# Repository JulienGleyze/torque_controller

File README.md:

## This repo contains the kicad project for my actuator's pcb controller, actuator image below

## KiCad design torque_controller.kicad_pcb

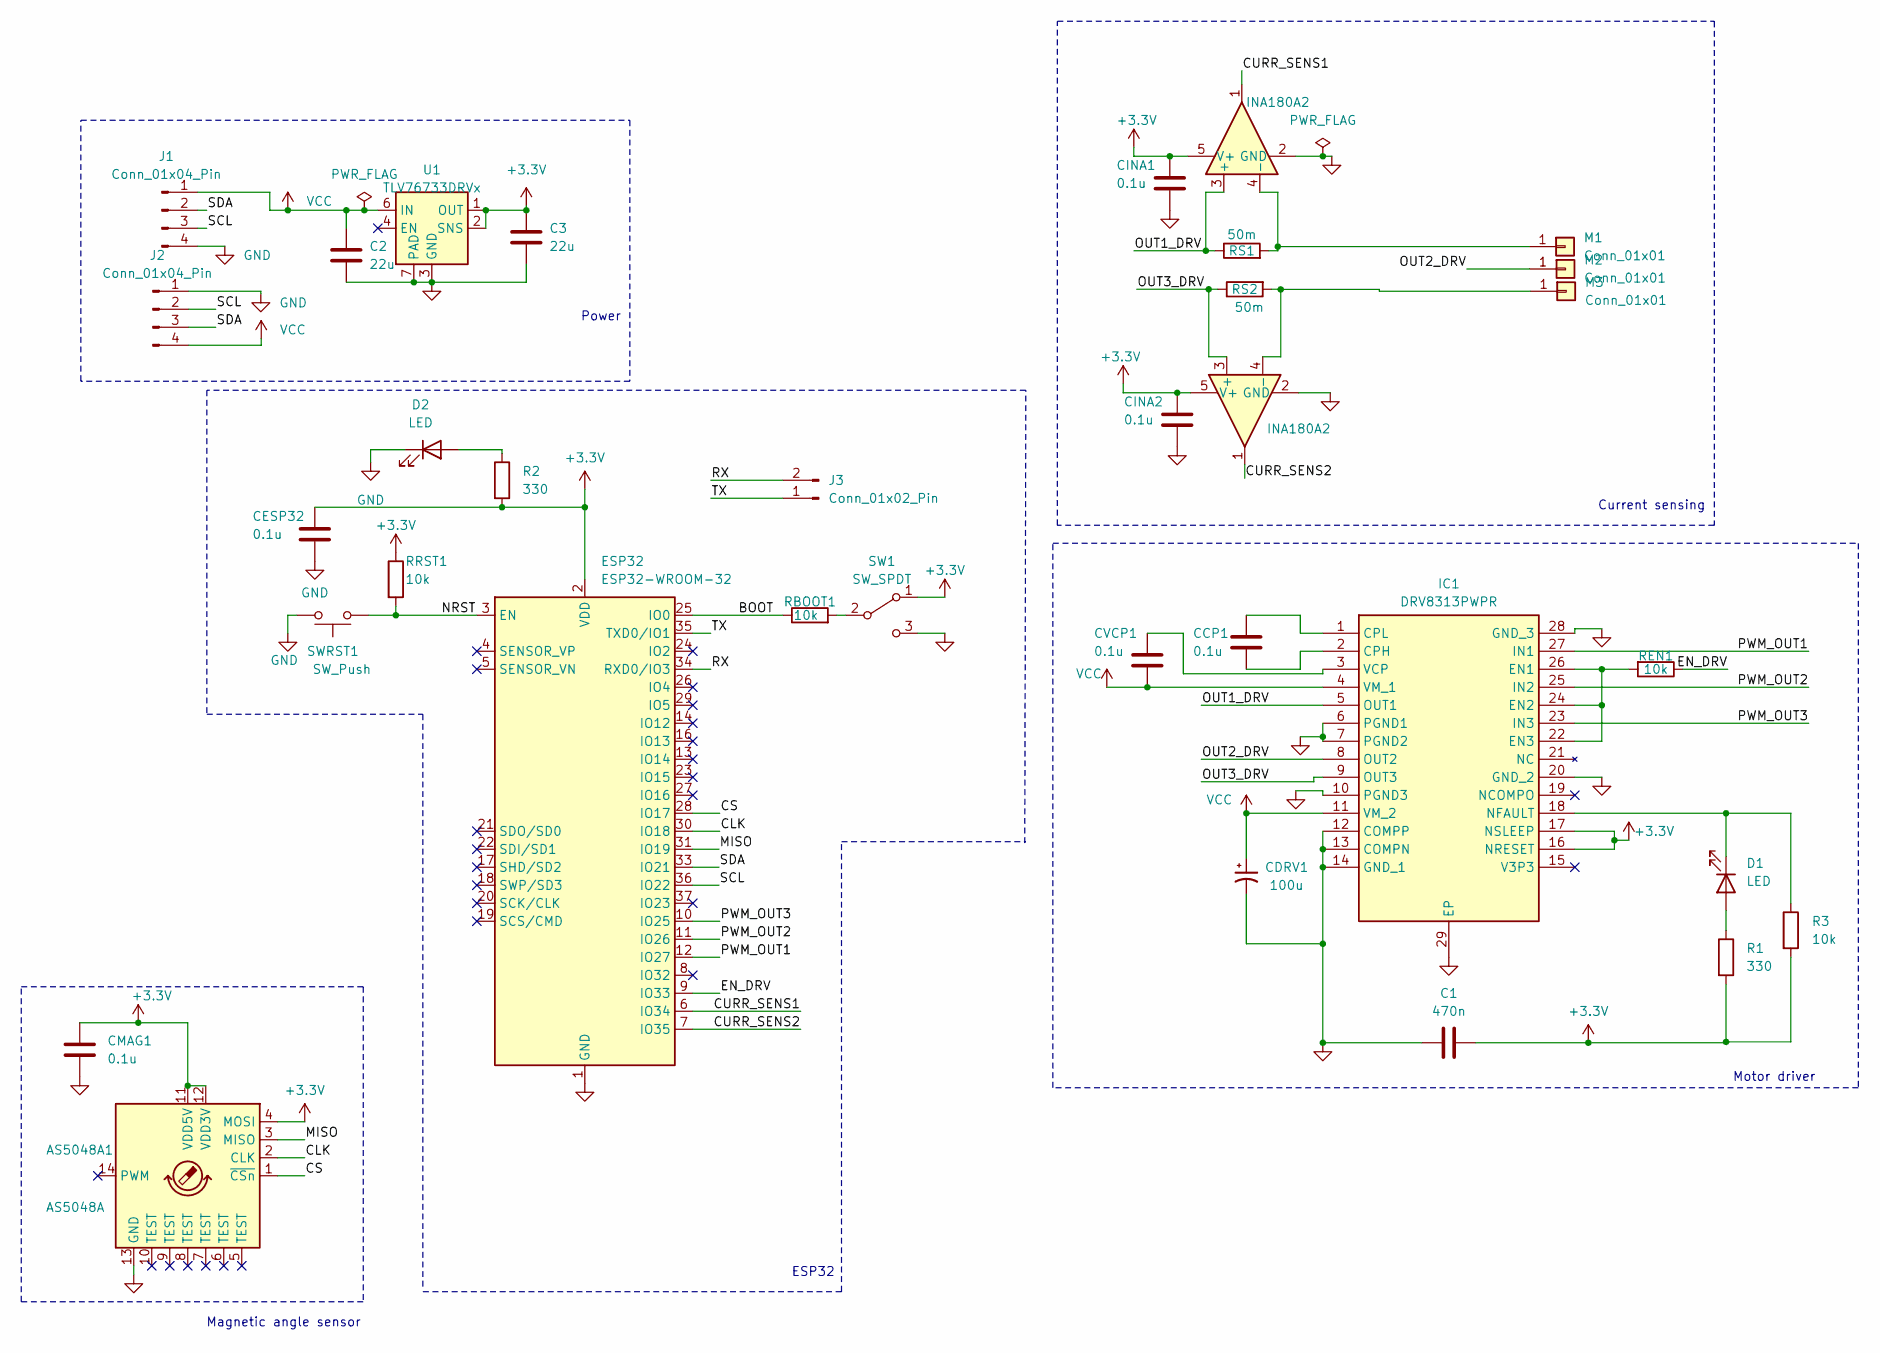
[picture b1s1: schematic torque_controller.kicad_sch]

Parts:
AS5048A1: AS5048A; TSSOP-14_4.4x5mm_P0.65mm
C1: 470n; C_0603_1608Metric
C2, C3: 22u; C_0603_1608Metric
CCP1: 0.1u; C_0603_1608Metric
CDRV1: 100u; CP_EIA-7343-31_Kemet-D
CESP32: 0.1u; C_0603_1608Metric
CINA1, CINA2: 0.1u; C_0603_1608Metric
CMAG1: 0.1u; C_0603_1608Metric
CVCP1: 0.1u; C_0603_1608Metric
D1, D2: LED; LED_0603_1608Metric
ESP32: ESP32-WROOM-32; ESP32-WROOM-32UE
IC1: DRV8313PWPR; SOP65P640X120-29N; Manufacturer_Part_Number DRV8313PWPR; Mouser Part Number 595-DRV8313PWPR
J1, J2: Conn_01x04_Pin; PinHeader_1x04_P2.00mm_Vertical_SMD_aligned
J3: Conn_01x02_Pin; PinHeader_1x02_P2.54mm_Vertical
M1, M2, M3: Conn_01x01; TestPoint_Pad_2.0x2.0mm
R1, R2: 330; R_0603_1608Metric
R3: 10k; R_0603_1608Metric
RBOOT1: 10k; R_0603_1608Metric
REN1: 10k; R_0603_1608Metric
RRST1: 10k; R_0603_1608Metric
RS1, RS2: 50m; R_1206_3216Metric
SW1: SW_SPDT; SW_SPDT_PCM12
SWRST1: SW_Push; SW_Tactile_SPST_NO_Straight_CK_PTS636Sx25SMTRLFS
U1: TLV76733DRVx; WSON-6-1EP_2x2mm_P0.65mm_EP1x1.6mm_ThermalVias
U2, U3: INA180A2; SOT-23-5

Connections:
+3.3V: AS5048A1.4 (MOSI), AS5048A1.11 (VDD5V), AS5048A1.12 (VDD3V), C1.2, C3.1, CESP32.2, CINA1.2, CINA2.2, CMAG1.1, ESP32.2 (VDD), IC1.16 (NRESET), IC1.17 (NSLEEP), R1.2, R2.2, R3.2, RRST1.1, SW1.1 (A), U1.1 (OUT), U1.2 (SNS), U2.5 (V+), U3.5 (V+)
/BOOT: ESP32.25 (IO0), RBOOT1.1
/CLK: AS5048A1.2 (CLK), ESP32.30 (IO18)
/CS: AS5048A1.1 (~CSn), ESP32.28 (IO17)
/CURR_SENS1: ESP32.6 (IO34), U2.1
/CURR_SENS2: ESP32.7 (IO35), U3.1
/EN_DRV: ESP32.9 (IO33), REN1.1
/MISO: AS5048A1.3 (MISO), ESP32.31 (IO19)
/NRST: ESP32.3 (EN), RRST1.2, SWRST1.1
/OUT1_DRV: IC1.5 (OUT1), RS1.1, U2.3 (+)
/OUT2_DRV: IC1.8 (OUT2), M2.1
/OUT3_DRV: IC1.9 (OUT3), RS2.1, U3.3 (+)
/PWM_OUT1: ESP32.12 (IO27), IC1.27 (IN1)
/PWM_OUT2: ESP32.11 (IO26), IC1.25 (IN2)
/PWM_OUT3: ESP32.10 (IO25), IC1.23 (IN3)
/RX: ESP32.34 (RXD0/IO3), J3.2
/SCL: ESP32.36 (IO22), J1.3, J2.2
/SDA: ESP32.33 (IO21), J1.2, J2.3
/TX: ESP32.35 (TXD0/IO1), J3.1
GND: AS5048A1.13 (GND), C1.1, C2.2, C3.2, CDRV1.2, CESP32.1, CINA1.1, CINA2.1, CMAG1.2, D2.1 (K), ESP32.1 (GND), ESP32.15 (GND), ESP32.38 (GND), ESP32.39 (GND), IC1.6 (PGND1), IC1.7 (PGND2), IC1.10 (PGND3), IC1.12 (COMPP), IC1.13 (COMPN), IC1.14 (GND_1), IC1.20 (GND_2), IC1.28 (GND_3), IC1.29 (EP), J1.4, J2.1, SW1.3 (C), SWRST1.2, U1.3 (GND), U1.5 (GND), U1.7 (PAD), U2.2 (GND), U3.2 (GND)
unnamed: D1.2 (A), R1.1
unnamed: D1.1 (K), IC1.18 (NFAULT), R3.1
unnamed: D2.2 (A), R2.1
unnamed: CCP1.1, IC1.2 (CPH)
unnamed: CCP1.2, IC1.1 (CPL)
unnamed: IC1.22 (EN3), IC1.24 (EN2), IC1.26 (EN1), REN1.2
unnamed: CVCP1.1, IC1.3 (VCP)
unnamed: M1.1, RS1.2, U2.4 (-)
unnamed: M3.1, RS2.2, U3.4 (-)
unnamed: RBOOT1.2, SW1.2 (B)
VCC: C2.1, CDRV1.1, CVCP1.2, IC1.4 (VM_1), IC1.11 (VM_2), J1.1, J2.4, U1.6 (IN)

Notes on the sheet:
Power
Magnetic angle sensor
Motor driver
Current sensing
ESP32

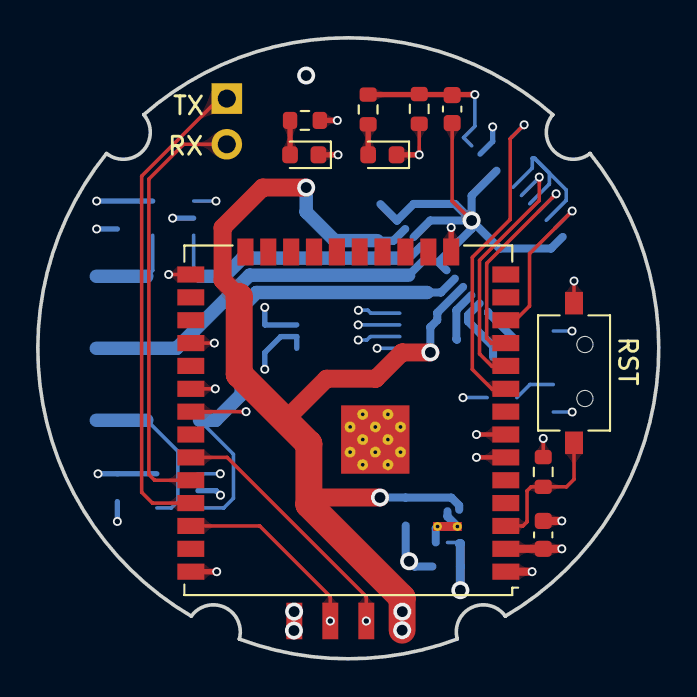
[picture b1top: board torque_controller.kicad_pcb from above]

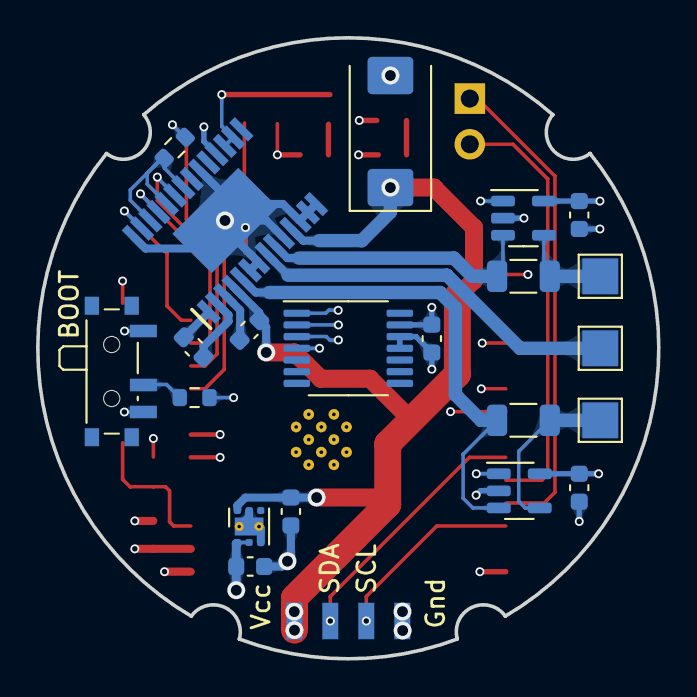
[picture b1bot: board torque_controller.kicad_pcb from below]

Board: 4 copper layers, 34.5 x 34.5 mm, 34 parts (22 on the bottom side), 31 nets.

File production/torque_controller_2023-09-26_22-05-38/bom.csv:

Designator,Footprint,Quantity,Value,LCSC Part #
AS5048A1,TSSOP-14_4.4x5mm_P0.65mm,1,AS5048A,
C1,0603,1,470n,
"C2, C3",0603,2,22u,
"CCP1, CESP32, CINA1, CINA2, CMAG1, CVCP1",0603,6,0.1u,
CDRV1,CP_EIA-7343-31_Kemet-D,1,100u,
"D1, D2",0603,2,LED,
ESP32,ESP32-WROOM-32UE,1,ESP32-WROOM-32,
IC1,SOP65P640X120-29N,1,DRV8313PWPR,
"J1, J2",PinHeader_1x04_P2.00mm_Vertical_SMD_aligned,2,Conn_01x04_Pin,
J3,PinHeader_1x02_P2.54mm_Vertical,1,Conn_01x02_Pin,
"M1, M2, M3",TestPoint_Pad_2.0x2.0mm,3,Conn_01x01,
"R1, R2",0603,2,330,
"R3, RBOOT1, REN1, RRST1",0603,4,10k,
"RS1, RS2",1206,2,50m,
SW1,SW_SPDT_PCM12,1,SW_SPDT,
SWRST1,SW_Tactile_SPST_NO_Straight_CK_PTS636Sx25SMTRLFS,1,SW_Push,
U1,WSON-6-1EP_2x2mm_P0.65mm_EP1x1.6mm_ThermalVias,1,TLV76733DRVx,
"U2, U3",SOT-23-5,2,INA180A2,

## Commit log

2023-10-10 actuator torque controller
2023-10-10 added readme
